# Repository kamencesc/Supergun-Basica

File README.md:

# Supergun-Basica
Diseño de una Supergun básica.

## Que es un Supergun?
Un Supergun nos permite conectar las antiguas placas de máquinas recreativas a un sistema adaptado, como puede ser a una TV, un monitor LCD, usando Gamepads de consolas, etc...

## Que hace este Supergun?
Tengo otro repositorio en el que intento crear una supergun lo mas completa posible, pero todo empieza por una base y este reprositorio es ela base del otro, por lo tanto tiene unas prestaciones muy básicas, como su propio nombre indica.

Dos puertos para joysticks arcade de 6 botones, 4 direcciones, Start y Select.

Entrada de 6 pins para conecta un Kick Harness.

Botón para seleccionar si jugar con el botón 6 del Kick Harness o de la placa arcade (ej. Bluelf)

Cambio de botones via hardware, nos permite poder cambiar la entre dos distribuciones de botones en el caso de usar un CPO del tipo 6 botones como los de Capcom. Mediante este cambio podemos asignar los 6 botones para usar un juego de lucha de Capcom (modo normal) o bien usar los dos primeros botones de la izquierda de las dos hileras, para juegos de lucha de NeoGeo de 4 botones. **Es importante que los switch estén siempre en la misma posición para evitar doblepulsación**

Salida Jack de 3,5" con selector para audio MONO o STEREO

Salida de video mediante terminales de tornillo, directa del connector JAMMA para su posprocesado externo (ej. usando una GBS8200 y adaptar video de CGA a VGA)

Entrada de corriente mediante terminales de tornillo, +5V +12V -5V y GND. Los -5V no suelen usarse pero lo dejamos por si alguna placa lo requiere.

La placa integra un connector para Kick Harness de CPS2 y así no tener que ir haciendo bricolaje. Este connector tiene que ir arrimado a la derecha del Kick Harness en el modulo CPS2.

Para facilitar la manipulación, se pueden usar switch/palancas externas, por ejemplo en una caja o en un mueble arcade, para así tener mas accesible la configuración de botones o los botones Credit, Test, Servicio y Select+ (cambio de juego en MVS multi cartucho).

# Agradecimientos
En este proyecto se ha usado el conector Jamma disponible en **Shinichi-Ohki** y disponible en su GitHub: https://github.com/Shinichi-Ohki/JAMMA_connector_for_eagle

Teneis un fork de su proyecto en mi github en el que he integrado conectores inversos (los que usa este supergun) y he suprimido el texto (que ademas tenia en la misma cara y lo hacía inteligible): https://github.com/kamencesc/JAMMA_connector_for_eagle

Los "pañeros" de _Crazy Lab_ por aguantar mis preguntas tontas...

**UNTESTED**

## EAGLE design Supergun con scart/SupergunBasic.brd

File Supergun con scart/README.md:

## Supergun con Scart
**UNTESTED**

Se ha realizado una versión del supergun con scart integrado. Este incluye todo lo del supergun básico ~~excepto que en vez de tener los terminales de RGB, disponemos de salida scart~~, seguimos disfrutando de salida jack 3.5" para el audio, si conectamos un jack, el audio del Scart queda deshabilitado.

Se han incluido Screw Terminals para dar salida a la señal directa del connector jamma, ademas de tener un selector de Sync, podemos seleccionar salida desde el potenciometro R10 o directo del jamma. En caso de usar los Screw Terminals y no se quiere instalar el scart, R5, R6, R7, R8 y R9 son completamente prescindibles.

~~Por espacio no se ha añadido un LM1881, sin prescindir de alguna otra opción no hay sitio en el diseño actual de la placa, se podria añadir a modo SMD pero lo que se pretende con esta placa es que sea de fácil montaje, con todos sus componentes DIP (con agujero).~~

Se ha añadido un LM1881 para Syn On Green en el scart, ademas hay un switch para seleccionar usar el LM1881 (CSYNC) o sync directo de jamma, esta última opción es para facilitar el uso con el OSSC.

Al igual que la versión básica se mantiene el Kick Harness para CPS2 (este Kick Harness es solo para los botones de patada y volumen, no para juegos de 4 Players), simplemente recortar las 2 placas adicionales, Soldar los pinheader correspondientes (hembra para la parte de CPS2 y la del supergun depende del usuario), soldar entre ellas los botones de patada del P1 y P2. La parte de CPS2 tiene para mapear botones de volumen (V- y V+).

Añadir que no todas las TVs pueden ser compatibles.

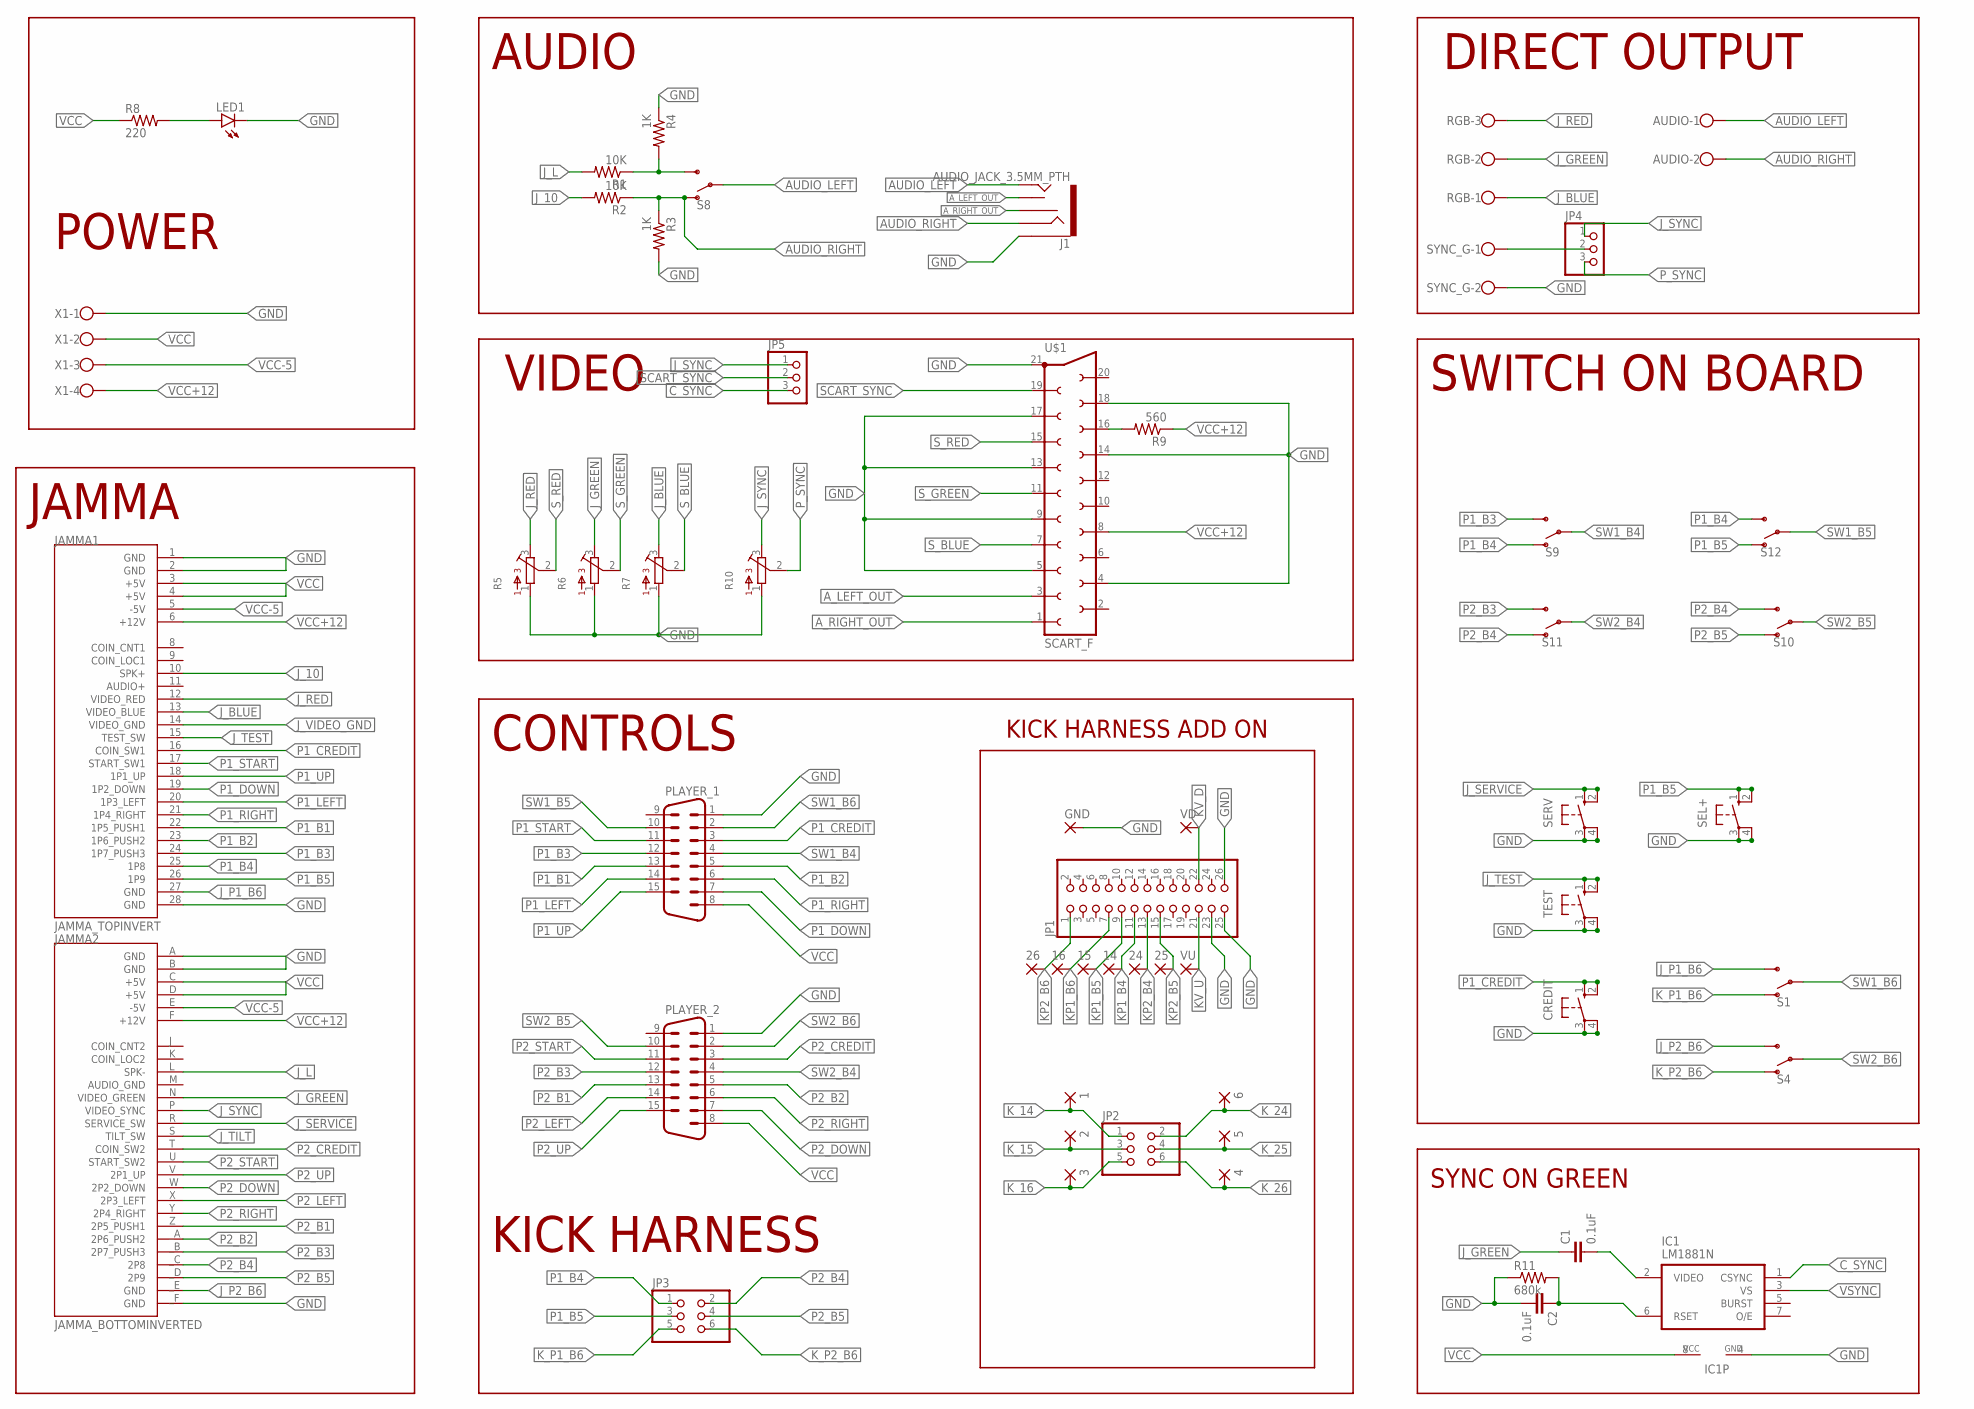
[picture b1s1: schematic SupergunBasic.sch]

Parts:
1, 2, 3, 4, 5, 6, 14, 15, 16, 24, 25, 26: SMD2; SMD1,27-2,54
AUDIO: W237-102
C1, C2: 0.1uF; CAP-PTH-SMALL-KIT
CREDIT: 10-XX; B3F-10XX
GND: SMD2; SMD1,27-2,54
IC1: LM1881N; DIL08
J1: AUDIO_JACK_3.5MM_PTH; AUDIO-JACK
JAMMA1: JAMMA_TOPINVERT; JAMMA_TOP_INV
JAMMA2: JAMMA_BOTTOMINVERTED; JAMMA_BOTTOM_INV
JP1: PINHD-2X13; 2X13
JP2, JP3: PINHD-2X3; 2X03
JP4, JP5: PINHD-1X3; 1X03
LED1: LEDLD260; LD260
PLAYER_1, PLAYER_2: M15HP
R1, R2: 10K; 0204/7
R3, R4: 1K; 0204/7
R5, R6, R7, R10: 3362P
R8: 220; 0204/7
R9: 560; 0204/7
R11: 680k; 0204/7
RGB: W237-103
S1, S4, S8, S9, S10, S11, S12: SWITCH-SPDT-PTH-11.6X4.0MM; SWITCH_SPDT_PTH_11.6X4.0MM
SEL+: 10-XX; B3F-10XX
SERV: 10-XX; B3F-10XX
SYNC_G: W237-102
TEST: 10-XX; B3F-10XX
U$1: SCART_F
VD: SMD2; SMD1,27-2,54
VU: SMD2; SMD1,27-2,54
X1: W237-4

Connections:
AUDIO_LEFT: AUDIO.1, J1.TIP, S8.2
AUDIO_RIGHT: AUDIO.2, J1.RING, R2.1, R3.1, S8.1 (O)
A_LEFT_OUT: J1.TSH, U$1.3
A_RIGHT_OUT: J1.RSH, U$1.1
C_SYNC: IC1.1 (CSYNC), JP5.3
DIRECT_SYNC: JP4.2, SYNC_G.1
GND: C2.2, CREDIT.3, CREDIT.4 (P1), GND.1, IC1.4 (GND), J1.SLEEVE, JAMMA1.1 (GND), JAMMA1.2 (GND), JAMMA1.28 (GND), JAMMA2.A (GND), JAMMA2.B (GND), JAMMA2._F (GND), JP1.23, JP1.25, JP1.26, LED1.K (C), PLAYER_1.1, PLAYER_2.1, R3.2, R4.1, R5.1, R6.1, R7.1, R10.1, R11.1, SEL+.3, SEL+.4 (P1), SERV.3, SERV.4 (P1), SYNC_G.2, TEST.3, TEST.4 (P1), U$1.4, U$1.5, U$1.9, U$1.13, U$1.14, U$1.17, U$1.18, U$1.21, X1.1
J_10: JAMMA1.10 (SPK+), R2.2
J_BLUE: JAMMA1.13 (VIDEO_BLUE), R7.3, RGB.1
J_GREEN: C1.1, JAMMA2.N (VIDEO_GREEN), R6.3, RGB.2
J_L: JAMMA2.L (SPK-), R1.2
J_P1_B6: JAMMA1.27 (GND), S1.3 (S)
J_P2_B6: JAMMA2._E (GND), S4.3 (S)
J_RED: JAMMA1.12 (VIDEO_RED), R5.3, RGB.3
J_SERVICE: JAMMA2.R (SERVICE_SW), SERV.1 (S), SERV.2 (S1)
J_SYNC: JAMMA2.P (VIDEO_SYNC), JP4.1, JP5.1, R10.3
J_TEST: JAMMA1.15 (TEST_SW), TEST.1 (S), TEST.2 (S1)
J_TILT: JAMMA2.S (TILT_SW)
J_VIDEO_GND: JAMMA1.14 (VIDEO_GND)
KP1_B4: 14.1, JP1.11
KP1_B5: 15.1, JP1.9
KP1_B6: 16.1, JP1.7
KP2_B4: 24.1, JP1.13
KP2_B5: 25.1, JP1.15
KP2_B6: 26.1, JP1.1
KV_D: JP1.22, VD.1
KV_U: JP1.21, VU.1
K_14: 1.1, JP2.1
K_15: 2.1, JP2.3
K_16: 3.1, JP2.5
K_24: 6.1, JP2.2
K_25: 5.1, JP2.4
K_26: 4.1, JP2.6
K_P1_B6: JP3.5, S1.1 (O)
K_P2_B6: JP3.6, S4.1 (O)
unnamed: LED1.A, R8.2
unnamed: C2.1, IC1.6 (RSET), R11.2
unnamed: C1.2, IC1.2 (VIDEO)
P1_B1: JAMMA1.22 (1P5_PUSH1), PLAYER_1.13
P1_B2: JAMMA1.23 (1P6_PUSH2), PLAYER_1.5
P1_B3: JAMMA1.24 (1P7_PUSH3), PLAYER_1.12, S9.3 (S)
P1_B4: JAMMA1.25 (1P8), JP3.1, S9.1 (O), S12.3 (S)
P1_B5: JAMMA1.26 (1P9), JP3.3, S12.1 (O), SEL+.1 (S), SEL+.2 (S1)
P1_CREDIT: CREDIT.1 (S), CREDIT.2 (S1), JAMMA1.16 (COIN_SW1), PLAYER_1.3
P1_DOWN: JAMMA1.19 (1P2_DOWN), PLAYER_1.7
P1_LEFT: JAMMA1.20 (1P3_LEFT), PLAYER_1.14
P1_RIGHT: JAMMA1.21 (1P4_RIGHT), PLAYER_1.6
P1_START: JAMMA1.17 (START_SW1), PLAYER_1.11
P1_UP: JAMMA1.18 (1P1_UP), PLAYER_1.15
P2_B1: JAMMA2.Z (2P5_PUSH1), PLAYER_2.13
P2_B2: JAMMA2._A (2P6_PUSH2), PLAYER_2.5
P2_B3: JAMMA2._B (2P7_PUSH3), PLAYER_2.12, S11.3 (S)
P2_B4: JAMMA2._C (2P8), JP3.2, S10.3 (S), S11.1 (O)
P2_B5: JAMMA2._D (2P9), JP3.4, S10.1 (O)
P2_CREDIT: JAMMA2.T (COIN_SW2), PLAYER_2.3
P2_DOWN: JAMMA2.W (2P2_DOWN), PLAYER_2.7
P2_LEFT: JAMMA2.X (2P3_LEFT), PLAYER_2.14
P2_RIGHT: JAMMA2.Y (2P4_RIGHT), PLAYER_2.6
P2_START: JAMMA2.U (START_SW2), PLAYER_2.11
P2_UP: JAMMA2.V (2P1_UP), PLAYER_2.15
P_SYNC: JP4.3, R10.2
SCART_FAST_SW: R9.2, U$1.16
SCART_SYNC: JP5.2, U$1.19
STR_LEFT: R1.1, R4.2, S8.3 (S)
SW1_B4: PLAYER_1.4, S9.2
SW1_B5: PLAYER_1.10, S12.2
SW1_B6: PLAYER_1.2, S1.2
SW2_B4: PLAYER_2.4, S11.2
SW2_B5: PLAYER_2.10, S10.2
SW2_B6: PLAYER_2.2, S4.2
S_BLUE: R7.2, U$1.7
S_GREEN: R6.2, U$1.11
S_RED: R5.2, U$1.15
VCC: IC1.8 (VCC), JAMMA1.3 (+5V), JAMMA1.4 (+5V), JAMMA2.C (+5V), JAMMA2.D (+5V), PLAYER_1.8, PLAYER_2.8, R8.1, X1.2
VCC+12: JAMMA1.6 (+12V), JAMMA2.F (+12V), R9.1, U$1.8, X1.4
VCC-5: JAMMA1.5 (-5V), JAMMA2.E (-5V), X1.3
VSYNC: IC1.3 (VS)

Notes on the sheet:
CONTROLS
SWITCH ON BOARD
JAMMA
VIDEO
AUDIO
POWER
KICK HARNESS
DIRECT OUTPUT
KICK HARNESS ADD ON
SYNC ON GREEN

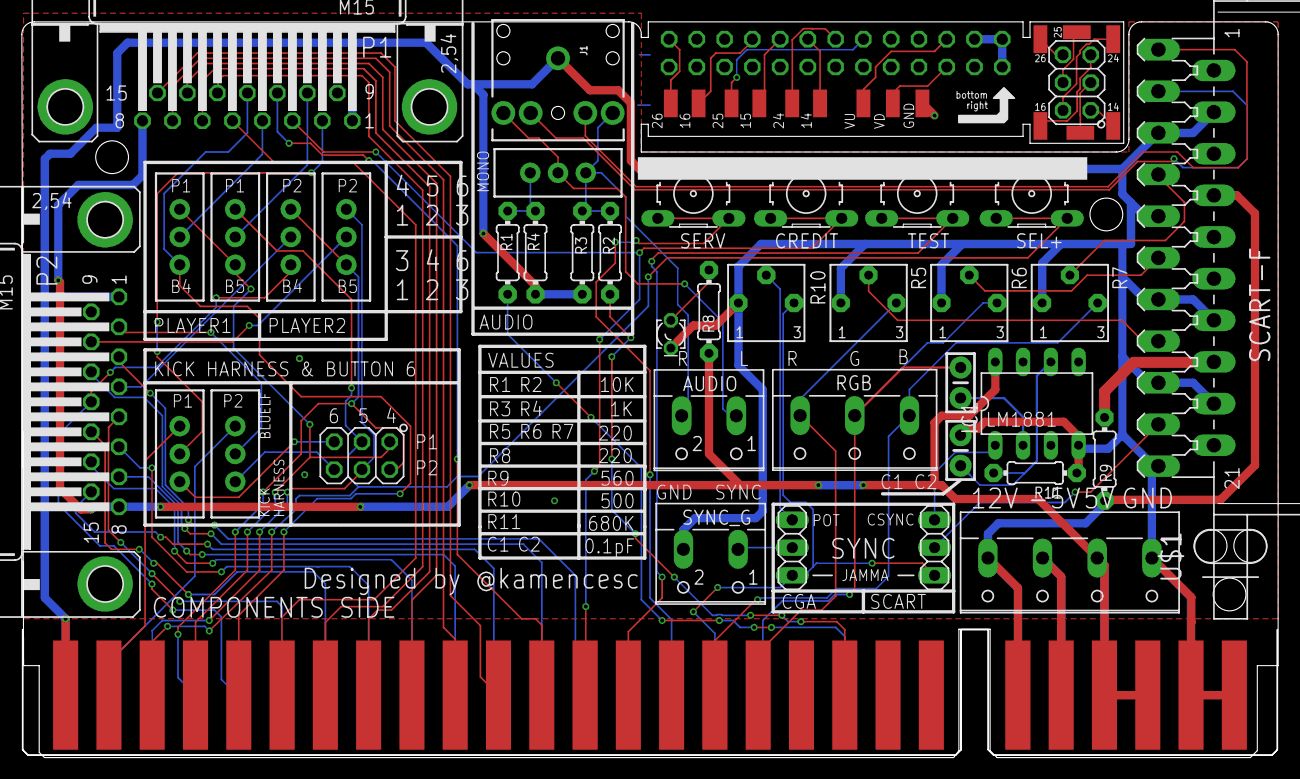
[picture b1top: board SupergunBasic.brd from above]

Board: 2 copper layers, 114.8 x 67.2 mm, 56 parts (1 on the bottom side), 74 nets.

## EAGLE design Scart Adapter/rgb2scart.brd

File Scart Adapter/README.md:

# Scart Adapter (jamma rgb2scart)
Con este adaptador tendremos señal de salida en SCART lista para connectar a una TV (no todas son compatibles).

Solo tenemos que llevar los siguientes señales

* R G B
* Sync
* 12V
* Audio R y L (con opción de usar un cable jack-jack, ideal por si usamos placas con salida de audio estereo directo como puede ser CPS2 o algunas MVS)

En la última versión disponible se ha añadido un LM1881 (AKA Sync Stripper) con montaje completamente opcional. El LM1881 usará el canal GREEN (sync on green) para generar una señal de sync mas limpia.

Para que el circuito funcioné como tal deberemos tener los jumpers J1 en posición 1-2 (o un switch si lo prefieres), los componentes son LM1881 en formato DIP8, dos condensadores de 0.1pF, una resistencia de 680k y por seguridad se ha añadido un REG1117 para usar 5V en el LM1881 (aunque tiene una tolerancia de 5-12V)

**UNTESTED**

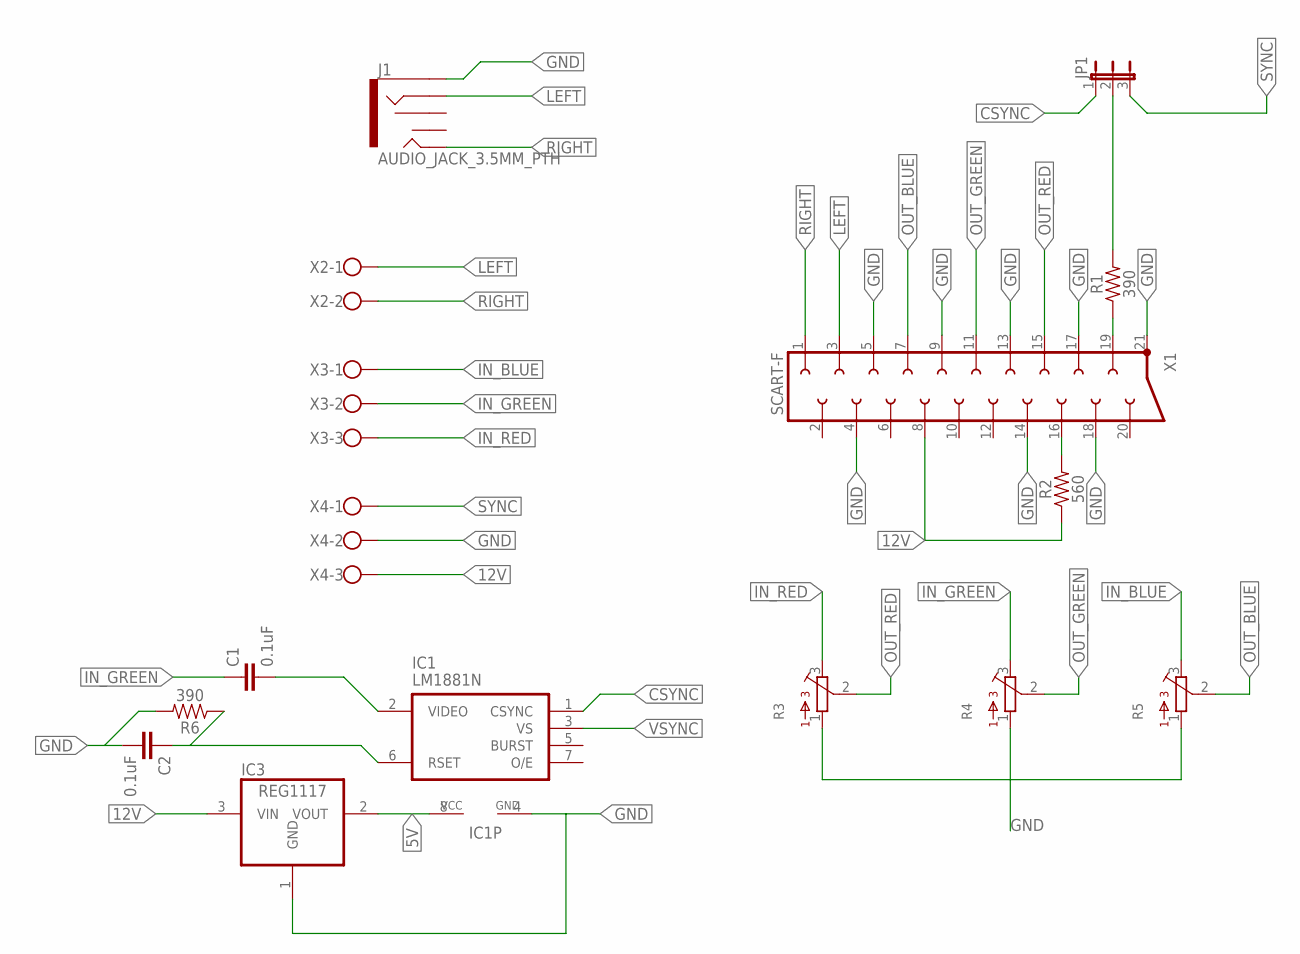
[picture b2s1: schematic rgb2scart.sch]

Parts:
C1, C2: 0.1uF; CAP-PTH-SMALL-KIT
IC1: LM1881N; DIL08
IC3: REG1117; SOT223
J1: AUDIO_JACK_3.5MM_PTH; AUDIO-JACK
JP1: JP2E; JP2
R1, R6: 390; AXIAL-0.3
R2: 560; AXIAL-0.3
R3, R4, R5: 3362P
X1: SCART-F
X2: W237-102
X3, X4: W237-103

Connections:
5V: IC1.8 (VCC), IC3.2 (VOUT)
12V: IC3.3 (VIN), R2.P$1 (1), X1.8, X4.3
CSYNC: IC1.1 (CSYNC), JP1.1
GND: C2.2, IC1.4 (GND), IC3.1 (GND), J1.SLEEVE, R3.1, R4.1, R5.1, R6.P$2 (2), X1.4, X1.5, X1.9, X1.13, X1.14, X1.17, X1.18, X1.21, X4.2
IN_BLUE: R5.3, X3.1
IN_GREEN: C1.1, R4.3, X3.2
IN_RED: R3.3, X3.3
LEFT: J1.RING, X1.3, X2.1
unnamed: JP1.2, R1.P$2 (2)
unnamed: C2.1, IC1.6 (RSET), R6.P$1 (1)
unnamed: C1.2, IC1.2 (VIDEO)
unnamed: R2.P$2 (2), X1.16
unnamed: R1.P$1 (1), X1.19
OUT_BLUE: R5.2, X1.7
OUT_GREEN: R4.2, X1.11
OUT_RED: R3.2, X1.15
RIGHT: J1.TIP, X1.1, X2.2
SYNC: JP1.3, X4.1
VSYNC: IC1.3 (VS)

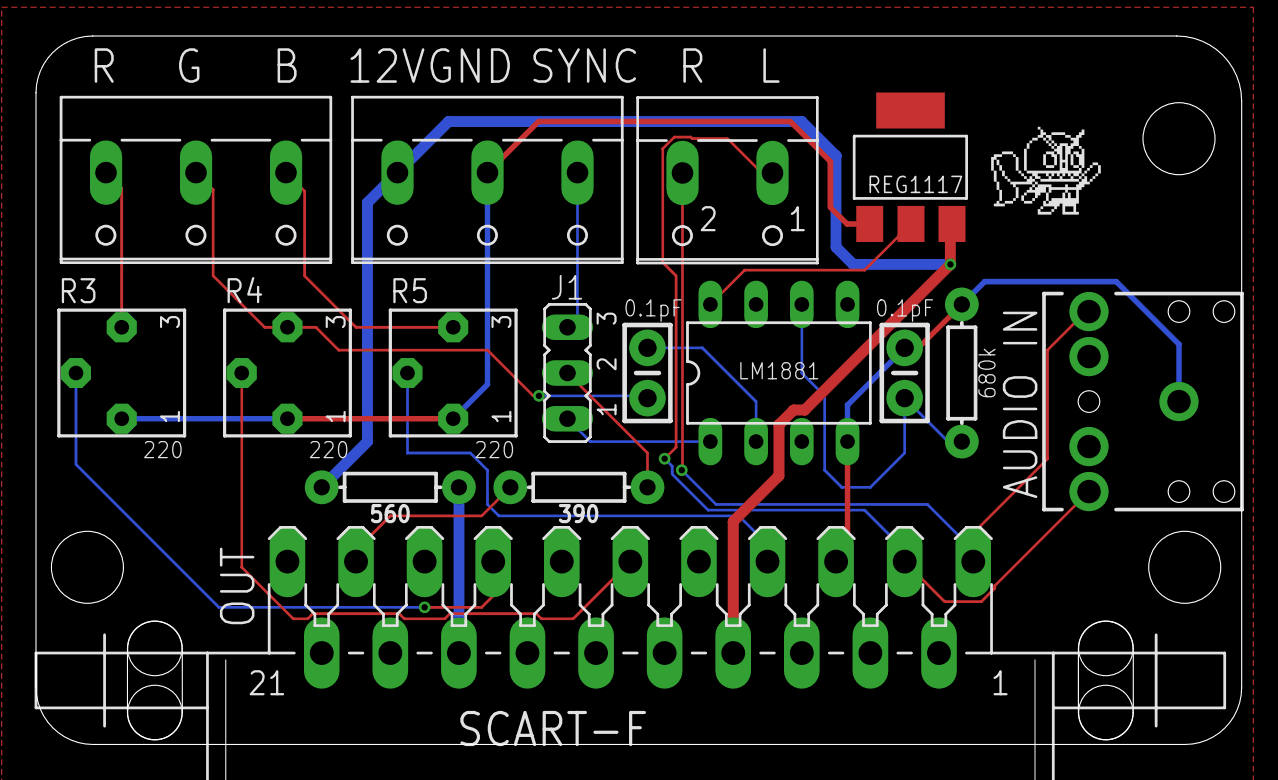
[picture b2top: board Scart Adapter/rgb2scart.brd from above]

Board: 2 copper layers, 67.0 x 39.4 mm, 16 parts (0 on the bottom side), 18 nets.

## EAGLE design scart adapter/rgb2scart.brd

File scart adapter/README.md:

# Scart Adapter (jamma rgb2scart)
Con este adaptador tendremos señal de salida en SCART lista para connectar a una TV (no todas son compatibles).

Solo tenemos que llevar los siguientes señales

* R G B
* Sync
* 12V
* Audio R y L (con opción de usar un cable jack-jack)

**UNTESTED**

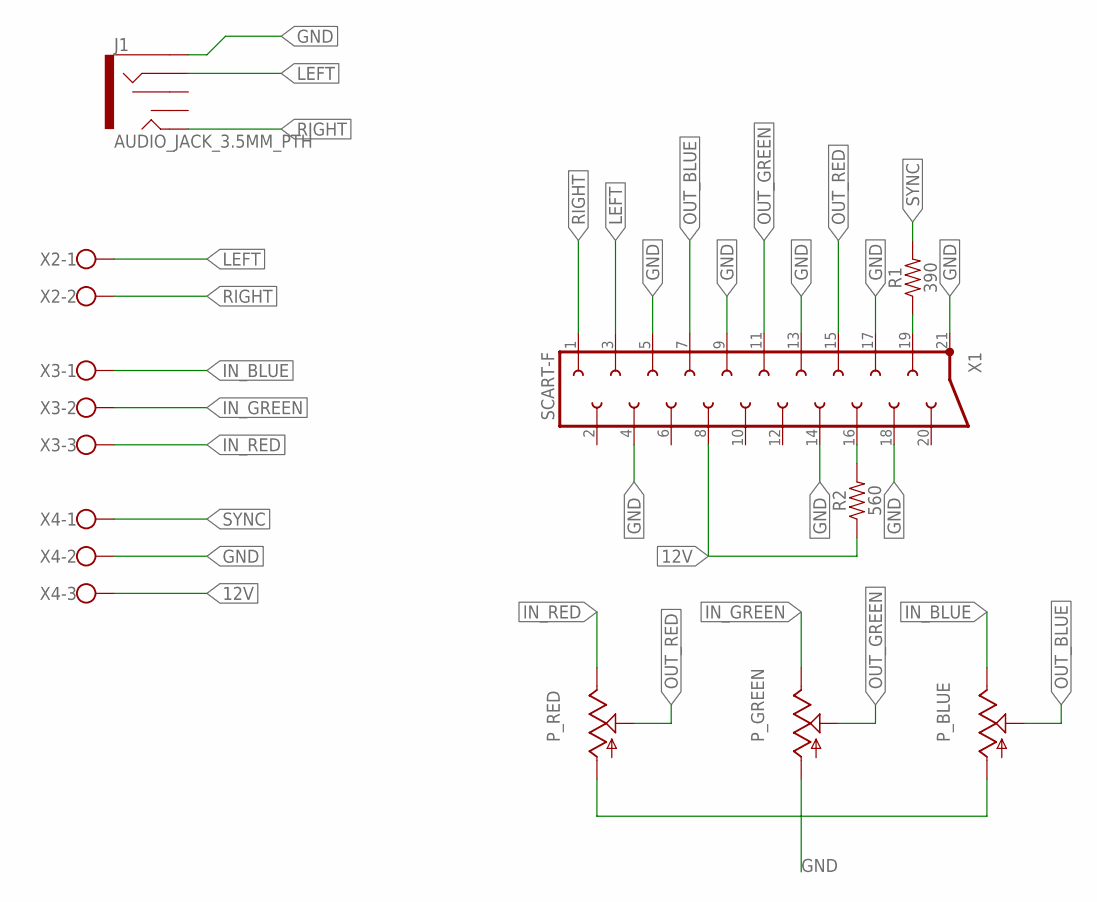
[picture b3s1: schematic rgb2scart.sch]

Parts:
J1: AUDIO_JACK_3.5MM_PTH; AUDIO-JACK
P_BLUE: TRIM_US-PT-10; PT-10
P_GREEN: TRIM_US-PT-10; PT-10
P_RED: TRIM_US-PT-10; PT-10
R1: 390; AXIAL-0.3
R2: 560; AXIAL-0.3
X1: SCART-F
X2: W237-102
X3, X4: W237-103

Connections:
12V: R2.P$1 (1), X1.8, X4.3
GND: J1.SLEEVE, P_BLUE.A, P_GREEN.A, P_RED.A, X1.4, X1.5, X1.9, X1.13, X1.14, X1.17, X1.18, X1.21, X4.2
IN_BLUE: P_BLUE.E, X3.1
IN_GREEN: P_GREEN.E, X3.2
IN_RED: P_RED.E, X3.3
LEFT: J1.RING, X1.3, X2.1
unnamed: R2.P$2 (2), X1.16
unnamed: R1.P$1 (1), X1.19
OUT_BLUE: P_BLUE.S, X1.7
OUT_GREEN: P_GREEN.S, X1.11
OUT_RED: P_RED.S, X1.15
RIGHT: J1.TIP, X1.1, X2.2
SYNC: R1.P$2 (2), X4.1

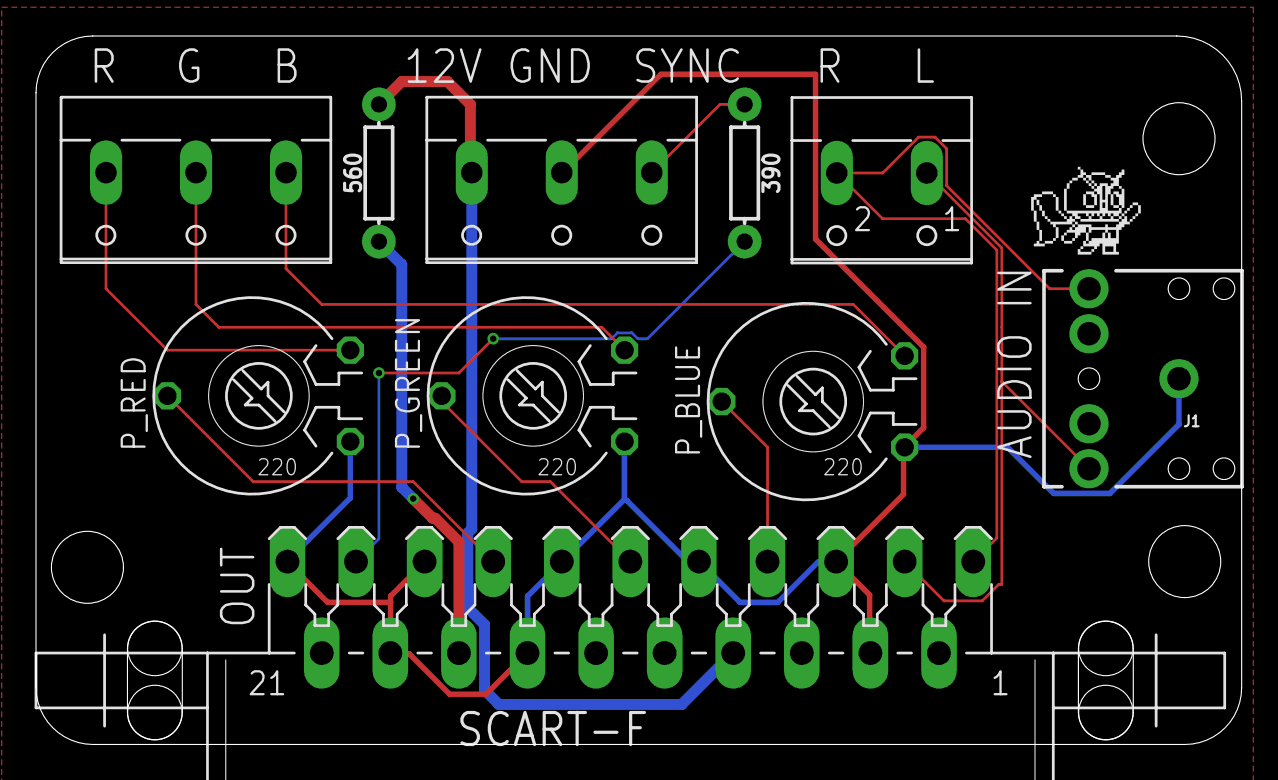
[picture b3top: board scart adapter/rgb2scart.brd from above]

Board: 2 copper layers, 67.0 x 39.4 mm, 10 parts (0 on the bottom side), 13 nets.

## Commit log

2019-05-03 SCH & BRD
    Primera versión de esta supergun básica, subidos sch y brd.
2019-05-03 Update README.md
    Actualizada información.
2019-05-03 Delete SupergunBasic.brd
    Error de diseño....
2019-05-05 rgb2scart para jamma
    Añadido el SCH y el BRD
2019-05-05 Supergun Basica
    Añadidos el sch y brd, se ha corregido el error detectado en el puerto JAMMA (estaba invertido), ahora se puede soldar un connector JAMMA hembra para así conectar directamente nuestras placas JAMMA.
2019-05-05 Add files via upload
    Se han marcado unos puntos en la PCB por si se quiere tener salida directa RGB del jamma en el caso de no querer usar el Scart
2019-05-07 Add files via upload
    Actualizados sch y brd.
    En el esquema se han icluïdo 2 subplacas que tienen que cortarse. Estas subplacas permiten conectarse al Kick Harness de CPS2. La pequeña va conectada a la Supergun (simplemente hacer coincidir los 2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
2019-06-06 Add files via upload
    Actualización
2019-06-06 Add files via upload
    He estado trabajando en la versión con Scart, es mas fácil quitar que añadir cosas, así que en el momento de subir esta versión, es identica a la Scart pero sin los requisitos de este.
2019-06-06 Rename scart adapter/README.md to Scart Adapter/README.md
2019-06-25 Add files via upload
    Minor changes
2019-08-27 Add files via upload
    There ara some changesr since las versión, now there's a lm1881 sync stripper to get Sync On Green to Scart Connector. But if you are using a OSSC theres a switch to select Jamma Sync (original) or C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
    Now there's a LED to bring light to the PCB!
    Minir improvements on design
2019-08-27 Add files via upload
    Optional LM1881 to scart connector, now you can select between lm1881 or jamma sync
    LED added
    Other improvements
2019-08-27 Add files via upload
    GND pad on the Kick Harness
2019-08-27 Add files via upload
    +12V Width changed to 30mil

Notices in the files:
parts and their libraries:
SparkFun-Resistors: Licensing: Creative Commons ShareAlike 4.0 International - https://creativecommons.org/licenses/by-sa/4.0
